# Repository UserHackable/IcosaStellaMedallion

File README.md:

## Icosa Stella Medallion

A version of this board was the first PCB I had manufactured, and the surface mount soldered the ATtiny85 and button to. 

This design is still my favorite for wearables, and has inspired may of my other 20 LED ATtiny85 Charlieplex boards. 

## IcosaStellaMedallion 

### Board dimensions

* (200000, 200000) original units
* (2.0000, 2.0000) inches
* (50.8000, 50.8000) mm

| Front | Back |
| --- | --- |
|  |  |

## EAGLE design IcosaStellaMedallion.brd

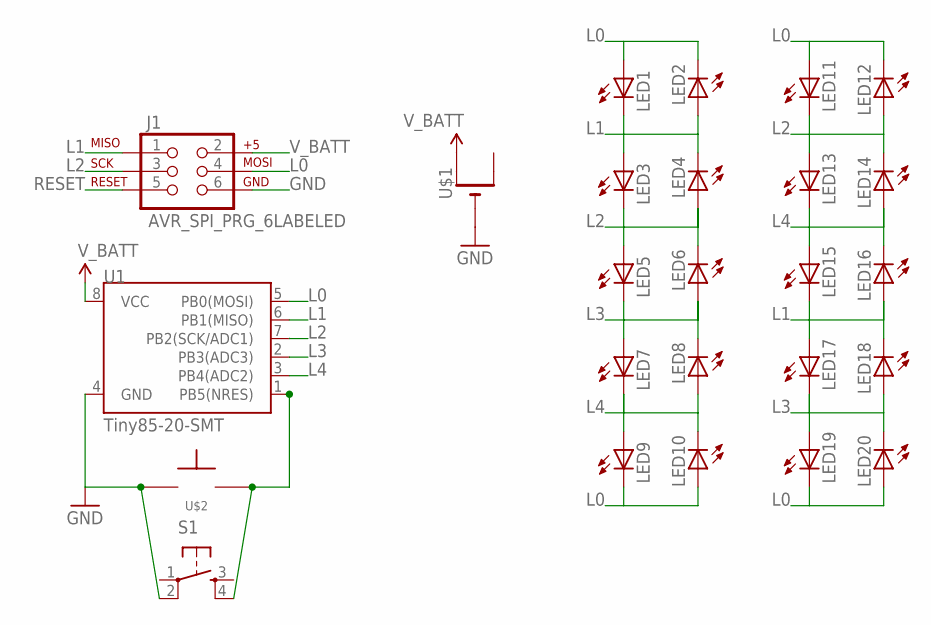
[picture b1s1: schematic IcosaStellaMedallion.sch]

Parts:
J1: AVR_SPI_PRG_6LABELED; 2X3-NS
LED1, LED2, LED3, LED4, LED5, LED6, LED7, LED8, LED9, LED10, LED11, LED12, LED13, LED14, LED15, LED16, LED17, LED18, LED19, LED20: LED5MM
S1: TAC_SWITCHSMD; TACTILE-SWITCH-SMD
U1: Tiny85-20-SMT; SO08-EIAJ
U$1: CR2032THM; CR2032-THRU
U$2: TAC_SPST_NOSMD; KXT

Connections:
GND: J1.6 (GND), S1.2, U1.4 (GND), U$1.-, U$2.1
L0: J1.4 (MOSI), LED1.A, LED2.K (C), LED9.K (C), LED10.A, LED11.A, LED12.K (C), LED19.K (C), LED20.A, U1.5 (PB0(MOSI))
L1: J1.1 (MISO), LED1.K (C), LED2.A, LED3.A, LED4.K (C), LED15.K (C), LED16.A, LED17.A, LED18.K (C), U1.6 (PB1(MISO))
L2: J1.3 (SCK), LED3.K (C), LED4.A, LED5.A, LED6.K (C), LED11.K (C), LED12.A, LED13.A, LED14.K (C), U1.7 (PB2(SCK/ADC1))
L3: LED5.K (C), LED6.A, LED7.A, LED8.K (C), LED17.K (C), LED18.A, LED19.A, LED20.K (C), U1.2 (PB3(ADC3))
L4: LED7.K (C), LED8.A, LED9.A, LED10.K (C), LED13.K (C), LED14.A, LED15.A, LED16.K (C), U1.3 (PB4(ADC2))
RESET: J1.5 (RST), S1.4, U1.1 (PB5(NRES)), U$2.2
V_BATT: J1.2 (V+), U1.8 (VCC), U$1.+1 (+)

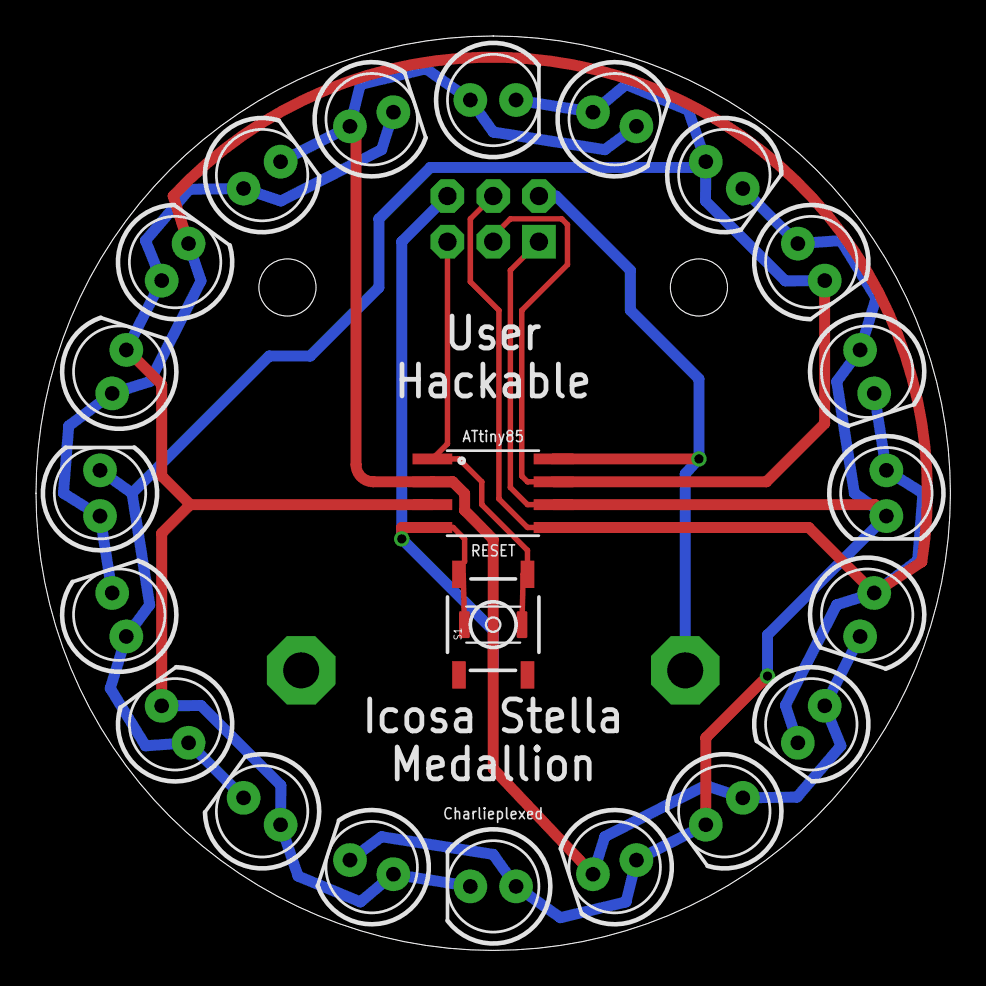
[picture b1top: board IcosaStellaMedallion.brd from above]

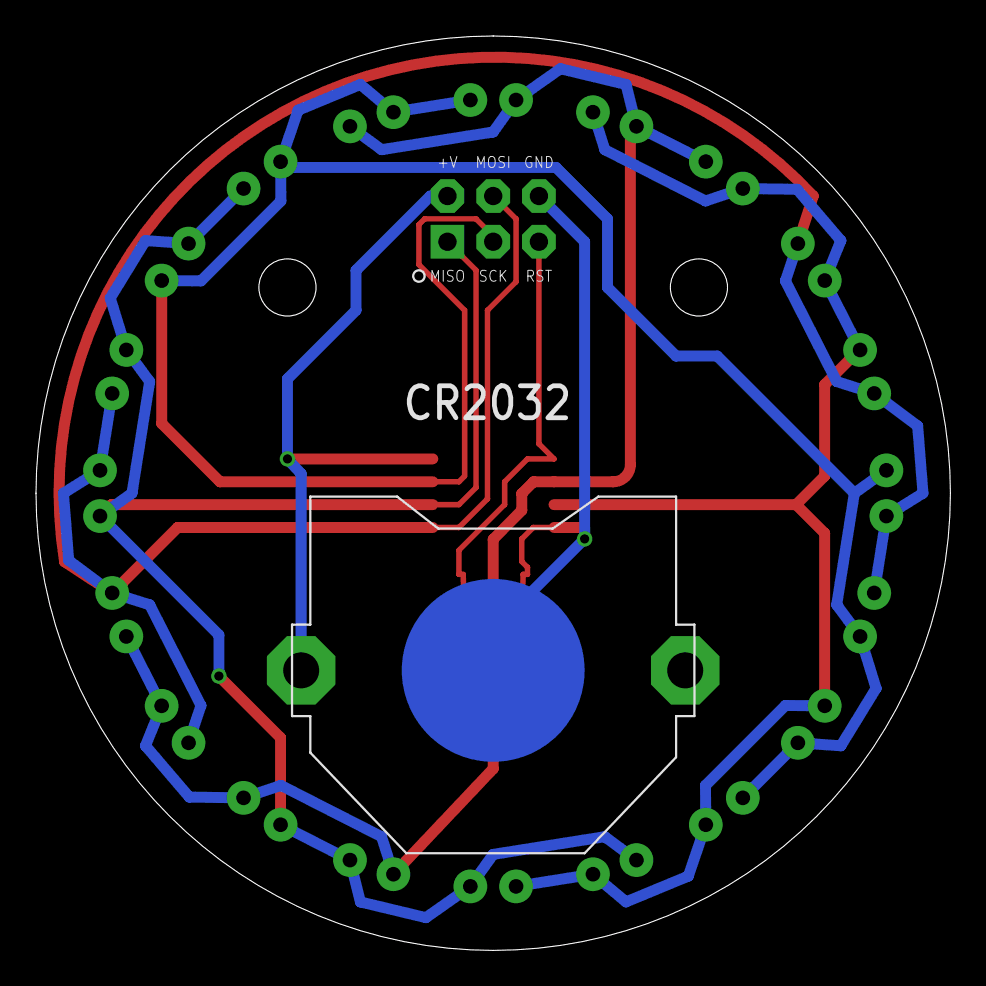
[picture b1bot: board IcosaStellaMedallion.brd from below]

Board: 2 copper layers, 50.8 x 50.8 mm, 25 parts (2 on the bottom side), 8 nets.

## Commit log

2016-04-08 from Makefile

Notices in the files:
parts and their libraries:
SparkFun-DigitalIC: Licensing: Creative Commons ShareAlike 4.0 International - https://creativecommons.org/licenses/by-sa/4.0
